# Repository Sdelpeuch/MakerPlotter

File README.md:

# MakerPlotter
Groupe maker 2021

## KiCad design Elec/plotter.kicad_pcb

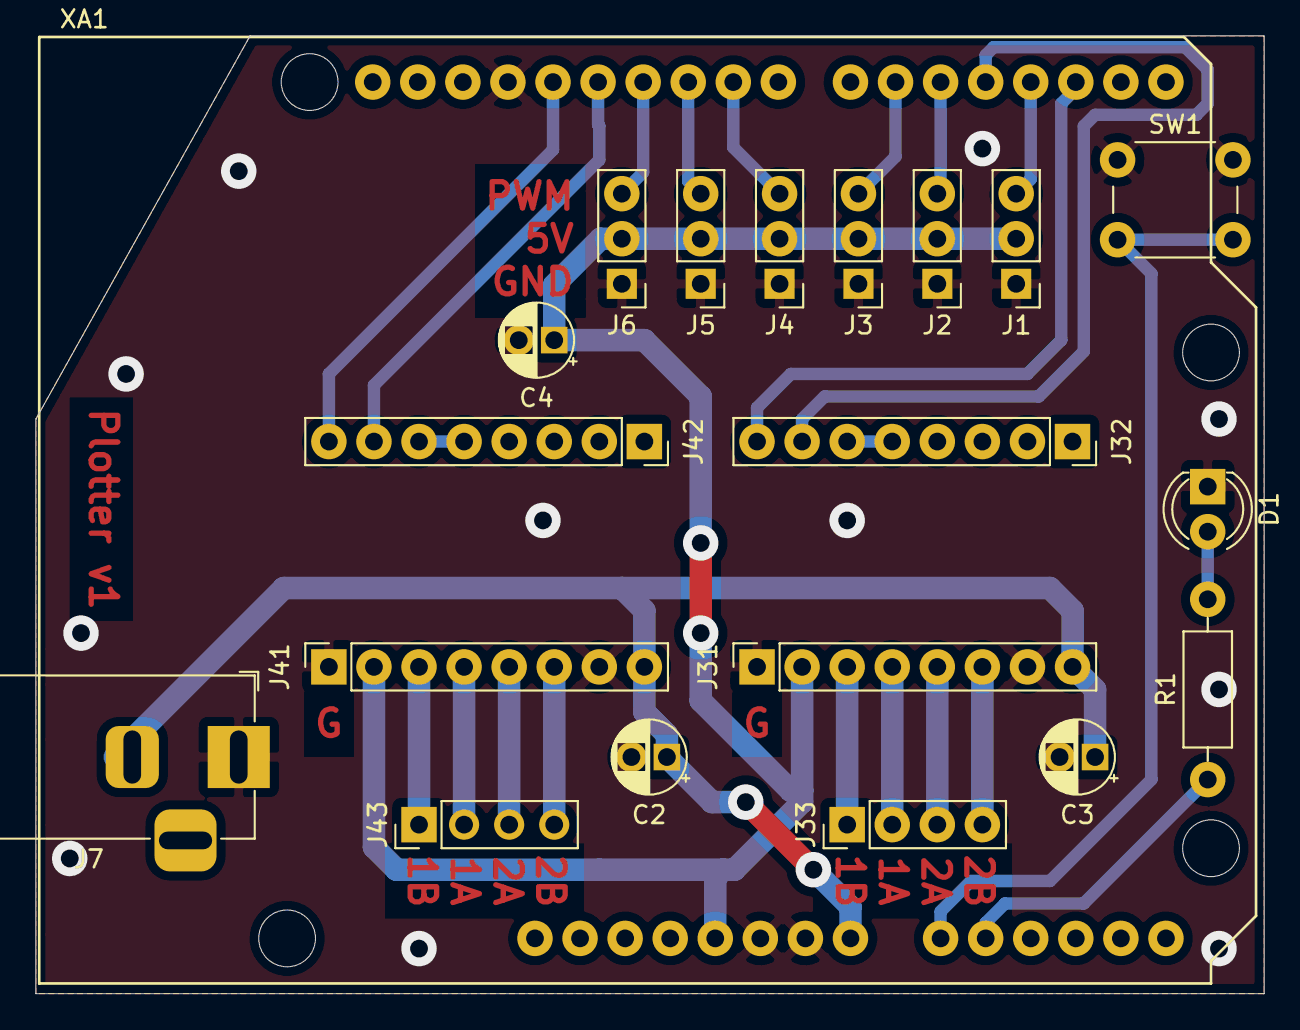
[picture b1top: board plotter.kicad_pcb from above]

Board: 2 copper layers, 69.2 x 54.0 mm, 20 parts (0 on the bottom side), 26 nets.

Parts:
C2, C3, C4: 100u; CP_Radial_D4.0mm_P2.00mm
D1: LED; LED_D4.0mm
J1, J2, J3, J4, J5, J6: Conn_01x03_Male; PinHeader_1x03_P2.54mm_Vertical
J7: Conn_01x02_Female; BarrelJack_Horizontal
J31, J32, J41, J42: Conn_01x08_Female; PinSocket_1x08_P2.54mm_Vertical
J33, J43: Conn_01x04_Male; PinHeader_1x04_P2.54mm_Vertical
R1: R; R_Axial_DIN0207_L6.3mm_D2.5mm_P10.16mm_Horizontal
SW1: SW_Push; SW_PUSH_6mm
XA1: Arduino_Uno_Shield

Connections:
+5V: C4.1, J1.2, J2.2, J3.2, J4.2, J5.2, J6.2, J31.2, J41.2, XA1.5V1
/Vpwr: C2.1, C3.1, J7.2, J31.8, J41.8, XA1.VIN
/dir1: J32.8, XA1.D2
/dir2: J42.8, XA1.D13
/pwm1: J1.3, XA1.D3
/pwm2: J2.3, XA1.D5
/pwm3: J3.3, XA1.D6
/pwm4: J4.3, XA1.D9
/pwm5: J5.3, XA1.D10
/pwm6: J6.3, XA1.D11
/step1: J32.7, XA1.D4
/step2: J42.7, XA1.D12
GND: C2.2, C3.2, C4.2, D1.1, J1.1, J2.1, J3.1, J4.1, J5.1, J6.1, J7.1, J31.1, J31.7, J41.1, J41.7, SW1.1, XA1.GND1, XA1.GND2, XA1.GND3
unnamed: D1.2, R1.2
unnamed: J31.3, J33.1
unnamed: J31.4, J33.2
unnamed: J31.5, J33.3
unnamed: J31.6, J33.4
unnamed: J32.5, J32.6
unnamed: J41.3, J43.1
unnamed: J41.4, J43.2
unnamed: J41.5, J43.3
unnamed: J41.6, J43.4
unnamed: J42.5, J42.6
unnamed: R1.1, XA1.A1
unnamed: SW1.2, XA1.A0

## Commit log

2021-03-31 FEAT(shield): add shield file
2021-03-31 Added meca
    Added SolidWorks 3d model, 3d parts to print and svg files for the lasercut
2021-03-31 FEAT(add): add meca folder
2021-03-31 Create LICENSE
2021-03-31 Added the file to lasercut (5mm)
2021-03-31 FEAT(platformio) : setup platformio for project
2021-03-31 FEAT(main): rework main (button not work)
2021-04-21 FEAT(setup): setup all classes
2021-04-21 FIX(platformio): add platformio.ini
2021-04-21 FIX(gitignore): add good gitignore
2021-04-28 FEAT(control): first stable version
2021-04-29 FIX(control): correct constant
2021-05-19 FEAT(control): add complex move and drawer
2021-05-19 FEAT(control): first stable version !
2021-05-19 FEAT(control): add aDraw
2021-05-19 FEAT(doc): add documentation
2021-05-19 feet(MECA) : 3d model and svg & stl files
2021-05-19 FEAT(info) : python script coordinates to cpp
2021-05-20 FIX(code) : fixed colors out of range
2021-05-20 FEAT(images) : deer template
2021-05-20 FEAT(images): add maker 2021 template
2021-05-20 FEAT(images) : otter template
2021-05-20 FEAT(images) : only stroke for otter
2021-05-20 FEAT(images) : Lion template
2021-05-20 FEAT(images) : map template
2021-05-20 FIX(images) : Lion & otter reupload
